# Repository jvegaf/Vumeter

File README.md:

# Vumeter

More info <a href="https://www.rinconingenieril.es/vumetro-por-etapas/"> https://www.rinconingenieril.es/vumetro-por-etapas/ </a>

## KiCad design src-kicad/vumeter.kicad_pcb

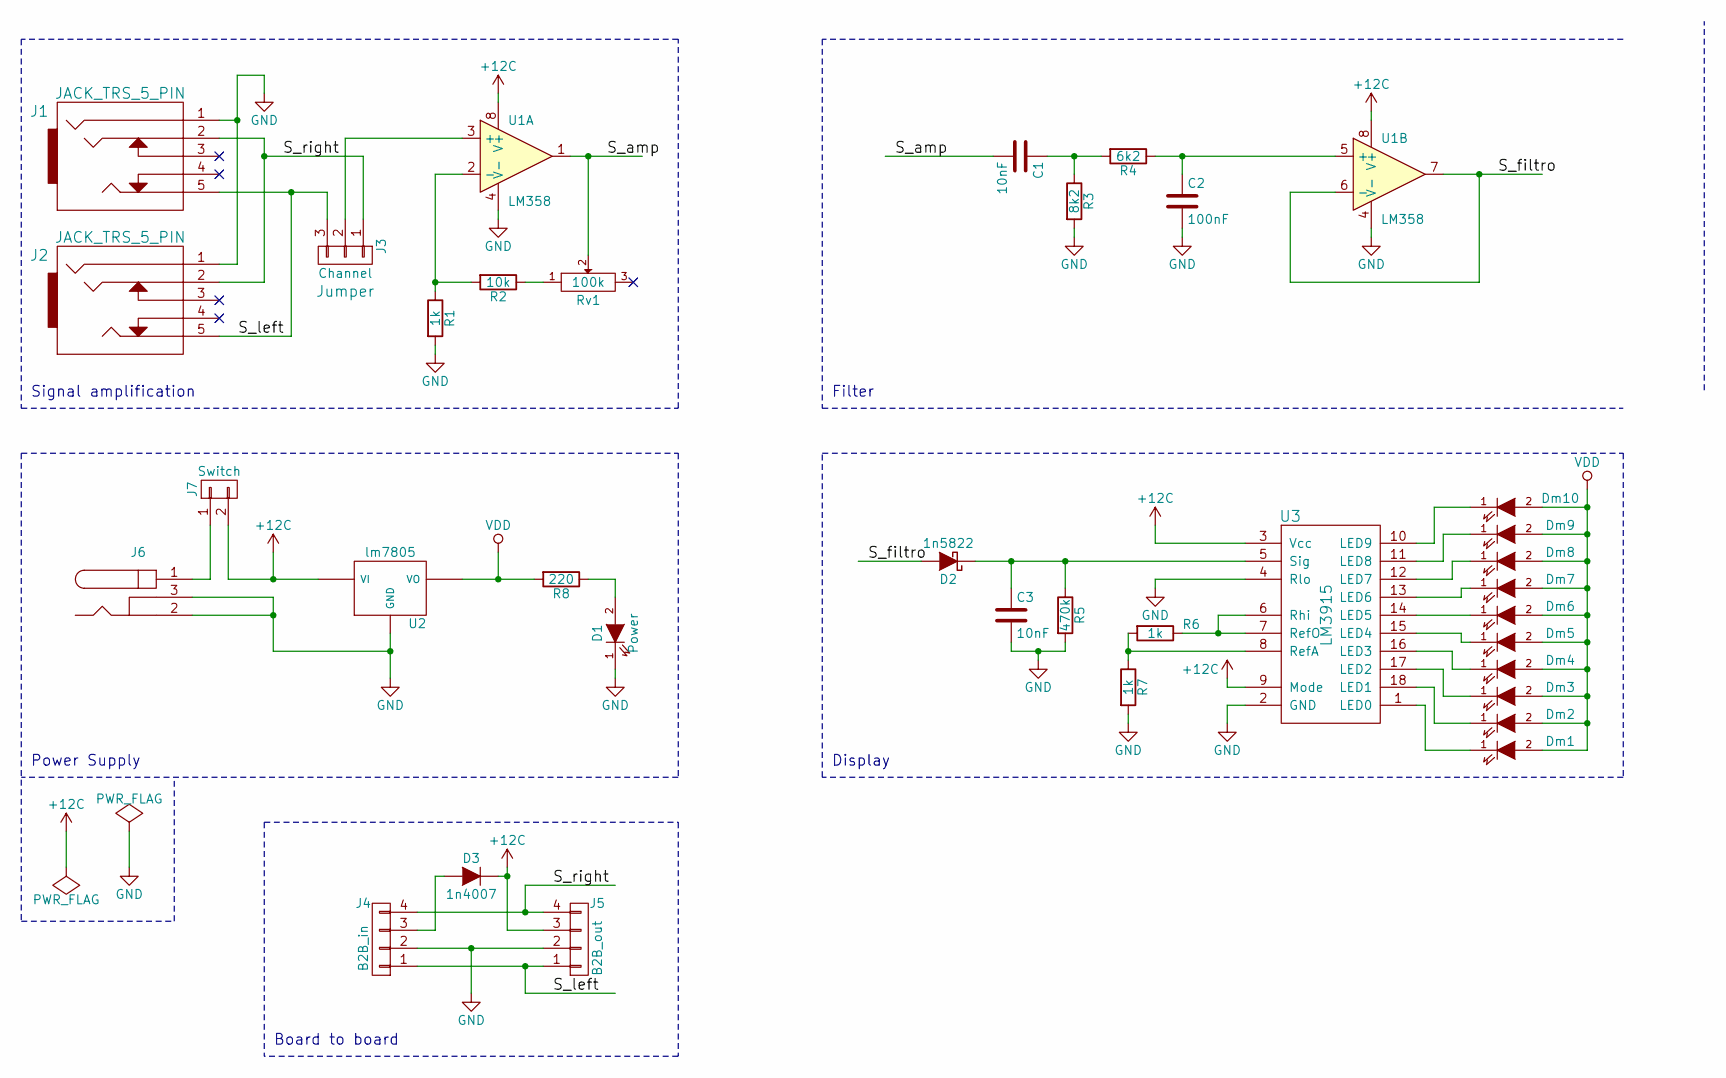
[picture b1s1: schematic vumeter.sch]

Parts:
1n4007: D3; D_A-405_P10.16mm_Horizontal
C1, C3: 10nF; C_Rect_L7.0mm_W2.0mm_P5.00mm
C2: 100nF; C_Rect_L7.0mm_W2.0mm_P5.00mm
D1: Power; LED_D5.0mm
D2: 1n5822; D_A-405_P10.16mm_Horizontal
Dm1, Dm2, Dm3, Dm4, Dm5, Dm6, Dm7, Dm8, Dm9, Dm10: LED; LED_D5.0mm
J1, J2: JACK_TRS_5_PIN; Jack_TRS_3.5mm_5_pin
J3: Channel; Pin_Header_Straight_1x03_Pitch2.54mm
J4: B2B_in; Pin_Header_Straight_1x04_Pitch2.54mm
J5: B2B_out; Pin_Header_Straight_1x04_Pitch2.54mm
J6: BARREL_JACK
J7: Switch; Pin_Header_Straight_1x02_Pitch2.54mm
R1, R6, R7: 1k; R_Axial_DIN0207_L6.3mm_D2.5mm_P2.54mm_Vertical
R2: 10k; R_Axial_DIN0207_L6.3mm_D2.5mm_P2.54mm_Vertical
R3: 8k2; R_Axial_DIN0207_L6.3mm_D2.5mm_P2.54mm_Vertical
R4: 6k2; R_Axial_DIN0207_L6.3mm_D2.5mm_P2.54mm_Vertical
R5: 470k; R_Axial_DIN0207_L6.3mm_D2.5mm_P2.54mm_Vertical
R8: 220; R_Axial_DIN0207_L6.3mm_D2.5mm_P2.54mm_Vertical
Rv1: 100k; Potentiometer_Trimmer_ACP_CA9h2.5_Vertical_Px2.5mm_Py5.0mm
U1: LM358; DIP-8_W7.62mm_LongPads
U2: lm7805; TO-220_Vertical
U3: LM3915; DIP-18_W7.62mm_LongPads

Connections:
+12C: 1n4007.1 (K), J5.3, J7.2, U1.8 (V+), U2.1 (VI), U3.3 (Vcc), U3.9 (Mode)
/S_amp: C1.2, Rv1.2, U1.1
/S_filtro: D2.2 (A), U1.6 (-), U1.7
/S_left: J1.5, J2.5, J3.3, J4.1, J5.1
/S_right: J1.2, J2.2, J3.1, J4.4, J5.4
GND: C2.2, C3.2, D1.1 (K), J1.1, J2.1, J4.2, J5.2, J6.2, J6.3, R1.2, R3.2, R5.2, R7.2, U1.4 (V-), U2.2 (GND), U3.2 (GND), U3.4 (Rlo)
unnamed: 1n4007.2 (A), J4.3
unnamed: C1.1, R3.1, R4.2
unnamed: C2.1, R4.1, U1.5 (+)
unnamed: C3.1, D2.1 (K), R5.1, U3.5 (Sig)
unnamed: D1.2 (A), R8.1
unnamed: Dm1.1 (K), U3.1 (LED0)
unnamed: Dm2.1 (K), U3.18 (LED1)
unnamed: Dm3.1 (K), U3.17 (LED2)
unnamed: Dm4.1 (K), U3.16 (LED3)
unnamed: Dm5.1 (K), U3.15 (LED4)
unnamed: Dm6.1 (K), U3.14 (LED5)
unnamed: Dm7.1 (K), U3.13 (LED6)
unnamed: Dm8.1 (K), U3.12 (LED7)
unnamed: Dm9.1 (K), U3.11 (LED8)
unnamed: Dm10.1 (K), U3.10 (LED9)
unnamed: J3.2, U1.3 (+)
unnamed: J6.1, J7.1
unnamed: R1.1, R2.2, U1.2 (-)
unnamed: R2.1, Rv1.1
unnamed: R6.1, U3.6 (Rhi), U3.7 (RefO)
unnamed: R6.2, R7.1, U3.8 (RefA)
VDD: Dm1.2 (A), Dm2.2 (A), Dm3.2 (A), Dm4.2 (A), Dm5.2 (A), Dm6.2 (A), Dm7.2 (A), Dm8.2 (A), Dm9.2 (A), Dm10.2 (A), R8.2, U2.3 (VO)

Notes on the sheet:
Power Supply
Signal amplification
Filter
Display
Board to board

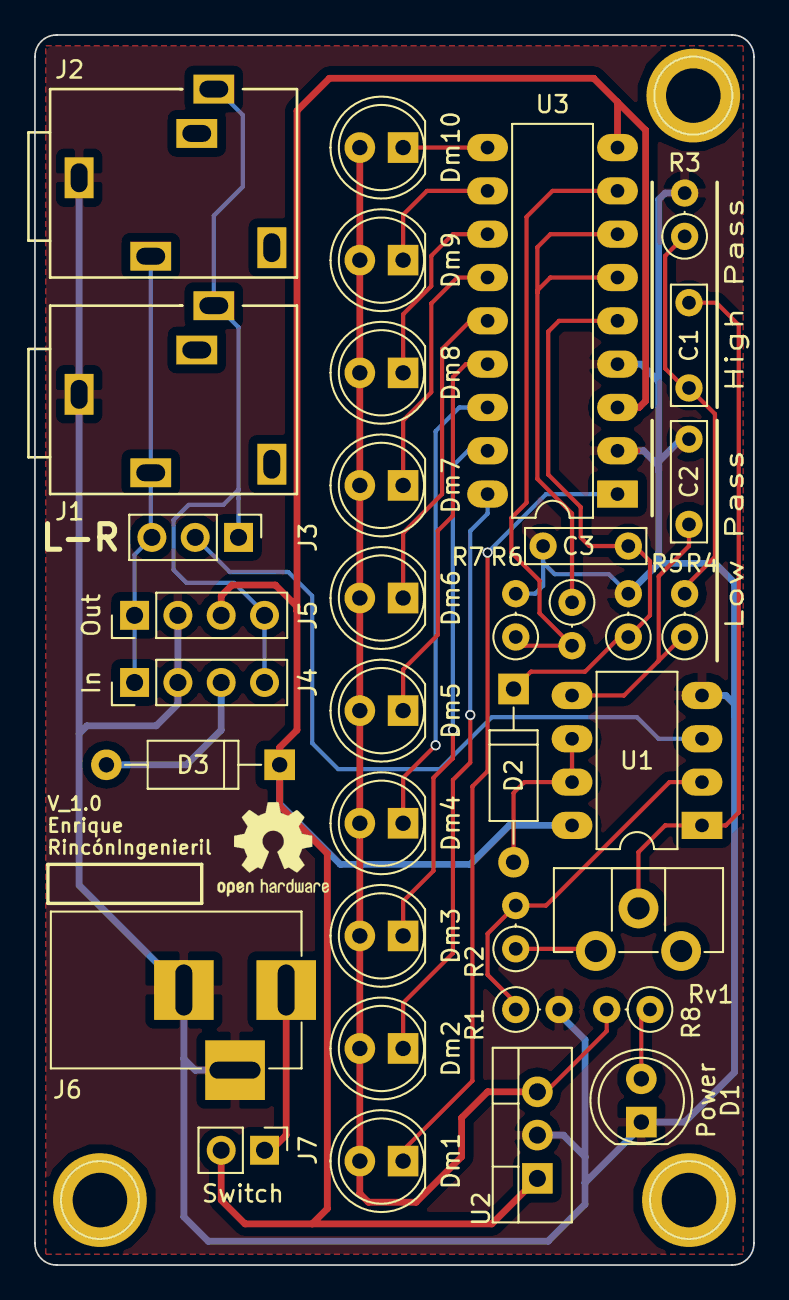
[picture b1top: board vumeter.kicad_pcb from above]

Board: 2 copper layers, 42.2 x 72.1 mm, 35 parts (0 on the bottom side), 28 nets.

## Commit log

2017-09-19 README update
2017-09-19 some mistakes
2017-09-30 3d update
2017-11-24 schematic modified now analyze stereo signal without lowpass and hipass filters.

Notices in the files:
src-kicad/vumeter.sch:
License: Creative Commons Attribution ShareAlike 4.0
